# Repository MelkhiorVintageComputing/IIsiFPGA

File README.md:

# A FPGA on a IIsi PDS card...

## Goal

The goal of this repository is to be able to interface a modern (2023 era) [FPGA](https://en.wikipedia.org/wiki/Field-programmable_gate_array) with a [Macintosh IIsi](https://en.wikipedia.org/wiki/Macintosh_IIsi) using its PDS (Processor Direct Slot) connector. The PDS is basically just a physical connector to the MC68030 memory bus.

So unless you're a retrocomputing enthusiast with such a machine, this is useless. If you are such an enthusiast, then maybe the ability to connect a modern LCD monitor using a digital interface to an old Macintosh might be of interest to you.

This project was 'spun off' the [NuBusFPGA](https://github.com/rdolbeau/NuBusFPGA), a similar project for the NuBus used in several models of Macintosh of the era. NuBusFPGA itself is a spin-off of the [SBusFPGA](https://github.com/rdolbeau/SBusFPGA), a similar project for the SBus used in Sun's SPARCstation.

## Current status

The HDMI (Highly Desirable Macintosh Interface) is working, with both video (single-hardware-res, multi-depth, windowboxed lower res) & audio working. More details are available in the readme of the NuBusFPGA repository.

There's also experimental support to expose 240 MiB of DDR3 as additional memory to the host system, but that requires a patched ROM, typically using a modern Flash-based 'ROM SIMM'. Burst reads are supported for that use case, reading 16 bytes at a time from the DDR3 using a dedicated port, giving X-1-1-1 burst timings.

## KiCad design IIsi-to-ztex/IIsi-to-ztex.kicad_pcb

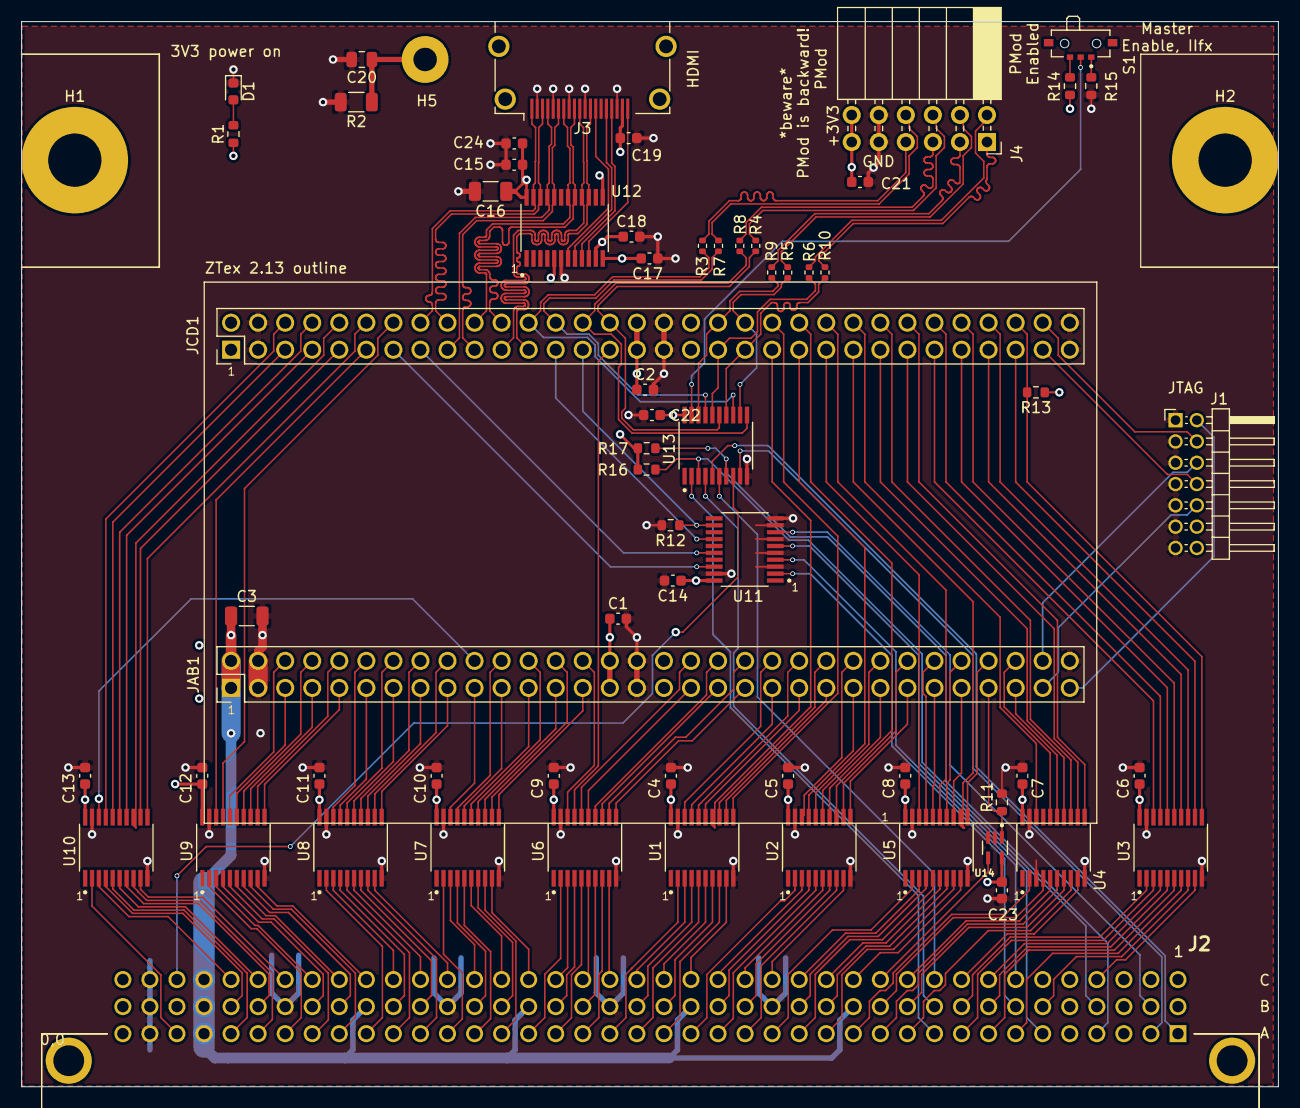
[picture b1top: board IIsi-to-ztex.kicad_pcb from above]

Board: 4 copper layers, 118.0 x 100.0 mm, 66 parts (0 on the bottom side), 218 nets.

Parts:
C1, C2, C4, C5, C6, C7, C8, C9, C10, C11, C12, C13, C14, C17, C18, C19, C21, C22, C23, C24: 100nF; C_0603_1608Metric
C3: 47uF 10V+; C_1206_3216Metric
C15: 10nF; C_0603_1608Metric
C16: 47uF 10V 1206; C_1206_3216Metric
C20: 10nF 1kV 0805; C_0805_2012Metric
D1: RED LED 0603; LED_0603_1608Metric
H1, H2: MountingHole_Pad; MountingHole_5mm_Pad
H5: MountingHole_Pad; MountingHole_2.2mm_M2_Pad
J1: Conn_02x07_Odd_Even; PinHeader_2x07_P2.00mm_Horizontal_For_SeeedStudio
J2: 650906-5; 6509065
J3: 10029449-111RLF (HDMI A); HDMI_A_Amphenol_10029449-111
J4: A2541HWR-2x6P (Pmod 2x6 F R); PinSocket_2x06_P2.54mm_Horizontal
JAB1: ZTEX_AB-ztex_AB; PinHeader_2x32_P2.54mm_Vertical_For_SeeedStudio
JCD1: ZTEX_CD-ztex_CD; PinHeader_2x32_P2.54mm_Vertical_For_SeeedStudio
R1: 560; R_0603_1608Metric
R2: 1M 500V 1206; R_1206_3216Metric
R3, R4, R5, R6, R7, R8, R9, R10: 22; R_0402_1005Metric
R11, R12, R13, R14, R15, R16, R17: 10k; R_0603_1608Metric
S1: SSAJ110100; SW_SSAJ110100
U1, U2, U3, U4, U5, U6, U7, U8, U9, U10, U11, U13: SN74CB3T3245PWR; SOP65P640X120-20N
U12: TPD12S016PWR; SOP65P640X120-24N
U14: SN74LV1T125DCKR; SOT65P210X110-5N

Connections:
+3V3: C1.1, C2.1, C4.1, C5.1, C6.1, C7.1, C8.1, C9.1, C10.1, C11.1, C12.1, C13.1, C14.1, C15.1, C16.1, C17.1, C21.1, C22.1, C23.2, C24.1, J4.11, J4.12, JAB1.29, JAB1.30, JAB1.33, JAB1.34, JCD1.31, JCD1.32, JCD1.35, JCD1.36, R1.1, R13.1, R14.1, U1.20, U2.20, U3.20, U4.20, U5.20, U6.20, U7.20, U8.20, U9.20, U10.20, U11.20, U12.5, U12.12, U12.24, U13.20, U14.5
+5V: C3.1, C18.1, J2.A37, J2.B13, J2.B19, J2.B25, J2.B31, J2.B37, J2.C37, JAB1.1, JAB1.2, R16.1, R17.1, U12.11
/B2B/JTAG_VIO: J1.2, JAB1.63
/HDMI/HDMI_5V: C19.1, J3.18, U12.13
/HDMI/cec_b: J3.13, U12.7
/HDMI/hpd_b: J3.19, U12.10
/HDMI/scl_b: J3.15, U12.8
/HDMI/sda_b: J3.16, U12.9
/pmod/P56+: J4.7, R7.1
/pmod/P56-: J4.8, R3.2
/pmod/P78+: J4.5, R8.1
/pmod/P78-: J4.6, R4.2
/pmod/P910+: J4.3, R9.1
/pmod/P910-: J4.4, R5.2
/pmod/P1112+: J4.1, R10.1
/pmod/P1112-: J4.2, R6.2
A0: J2.C36, U10.3
A0_3V3: JCD1.6, U10.17
A1: J2.B36, U10.4
A1_3V3: JCD1.5, U10.16
A2: J2.A36, U10.5
A2_3V3: JCD1.8, U10.15
A3: J2.C35, U10.6
A3_3V3: JCD1.7, U10.14
A4: J2.B35, U10.7
A4_3V3: JCD1.10, U10.13
A5: J2.A35, U10.8
A5_3V3: JCD1.9, U10.12
A6: J2.C34, U10.9
A6_3V3: JCD1.12, U10.11
A7: J2.A34, U9.2
A7_3V3: JCD1.11, U9.18
A8: J2.C33, U9.3
A8_3V3: JCD1.14, U9.17
A9: J2.B33, U9.4
A9_3V3: JAB1.6, U9.16
A10: J2.A33, U9.5
A10_3V3: JAB1.5, U9.15
A11: J2.C32, U9.6
A11_3V3: JAB1.8, U9.14
A12: J2.B32, U9.7
A12_3V3: JAB1.7, U9.13
A13: J2.A32, U9.8
A13_3V3: JAB1.10, U9.12
A14: J2.C31, U9.9
A14_3V3: JAB1.9, U9.11
A15: J2.A31, U8.2
A15_3V3: JAB1.12, U8.18
A16: J2.C30, U8.3
A16_3V3: JAB1.11, U8.17
A17: J2.B30, U8.4
A17_3V3: JAB1.14, U8.16
A18: J2.A30, U8.5
A18_3V3: JAB1.13, U8.15
A19: J2.C29, U8.6
A19_3V3: JAB1.16, U8.14
A20: J2.B29, U8.7
A20_3V3: JAB1.15, U8.13
A21: J2.A29, U8.8
A21_3V3: JAB1.18, U8.12
A22: J2.C28, U8.9
A22_3V3: JAB1.17, U8.11
A23: J2.A28, U7.2
A23_3V3: JAB1.19, U7.18
A24: J2.C27, U7.3
A24_3V3: JAB1.22, U7.17
A25: J2.B27, U7.4
A25_3V3: JAB1.21, U7.16
A26: J2.A27, U7.5
A26_3V3: JAB1.23, U7.15
A27: J2.C26, U7.6
A27_3V3: JAB1.24, U7.14
A28: J2.B26, U7.7
A28_3V3: JAB1.25, U7.13
A29: J2.A26, U7.8
A29_3V3: JAB1.26, U7.12
A30: J2.C25, U7.9
A30_3V3: JAB1.27, U7.11
A31: J2.A25, U6.2
A31_3V3: JAB1.28, U6.18
C16M: J2.C38, U13.8
C16M_3V3: JCD1.40, R5.1, U13.12
CACHE: J2.B2, U11.8
CACHE_3V3: JCD1.27, R12.1, U11.12
CPUCLK: J2.A38, U10.2
CPUCLK_3V3: JAB1.20, U10.18
D0: J2.A13, U4.2
D0_3V3: JCD1.48, U4.18
D1: J2.C13, U5.9
D1_3V3: JAB1.58, U5.11
D2: J2.A14, U5.8
D2_3V3: JCD1.47, U5.12
D3: J2.B14, U5.7
D3_3V3: JAB1.55, U5.13
D4: J2.C14, U5.6
D4_3V3: JAB1.56, U5.14
D5: J2.A15, U5.5
D5_3V3: JCD1.46, U5.15
D6: J2.B15, U5.4
D6_3V3: JAB1.53, U5.16
D7: J2.C15, U5.3
D7_3V3: JAB1.54, U5.17
D8: J2.A16, U5.2
D8_3V3: JCD1.45, U5.18
D9: J2.C16, U2.9
D9_3V3: JAB1.51, U2.11
D10: J2.A17, U2.8
D10_3V3: JAB1.52, U2.12
D11: J2.B17, U2.7
D11_3V3: JCD1.44, U2.13
D12: J2.C17, U2.6
D12_3V3: JAB1.49, U2.14
D13: J2.A18, U2.5
D13_3V3: JAB1.50, U2.15
D14: J2.B18, U2.4
D14_3V3: JCD1.43, U2.16
D15: J2.C18, U2.3
D15_3V3: JAB1.47, U2.17
D16: J2.A19, U2.2
D16_3V3: JAB1.48, U2.18
D17: J2.C19, U1.9
D17_3V3: JCD1.42, U1.11
D18: J2.A20, U1.8
D18_3V3: JAB1.45, U1.12
D19: J2.B20, U1.7
D19_3V3: JAB1.46, U1.13
D20: J2.C20, U1.6
D20_3V3: JCD1.41, U1.14
D21: J2.A21, U1.5
D21_3V3: JAB1.43, U1.15
D22: J2.B21, U1.4
D22_3V3: JAB1.44, U1.16
D23: J2.C21, U1.3
D23_3V3: JAB1.41, U1.17
D24: J2.A22, U1.2
D24_3V3: JAB1.42, U1.18
D25: J2.C22, U6.9
D25_3V3: JAB1.39, U6.11
D26: J2.A23, U6.8
D26_3V3: JAB1.40, U6.12
D27: J2.B23, U6.7
D27_3V3: JAB1.37, U6.13
D28: J2.C23, U6.6
D28_3V3: JAB1.38, U6.14
D29: J2.A24, U6.5
D29_3V3: JAB1.35, U6.15
D30: J2.B24, U6.4
D30_3V3: JAB1.36, U6.16
D31: J2.C24, U6.3
D31_3V3: JCD1.29, U6.17
FC0: J2.C11, U4.5
FC0_3V3: JAB1.59, U4.15
FC1: J2.B11, U4.7
FC1_3V3: JCD1.50, U4.13
FC2: J2.A11, U4.8
FC2_3V3: JCD1.51, U4.12
FPGA_JTAG_TCK: J1.6, JAB1.62
FPGA_JTAG_TDI: J1.10, JAB1.61
FPGA_JTAG_TDO: J1.8, JCD1.61
FPGA_JTAG_TMS: J1.4, JCD1.62
GND: C1.2, C2.2, C3.2, C4.2, C5.2, C6.2, C7.2, C8.2, C9.2, C10.2, C11.2, C12.2, C13.2, C14.2, C15.2, C16.2, C17.2, C18.2, C19.2, C20.2, C21.2, C22.2, C23.1, C24.2, D1.1, J1.1, J1.3, J1.5, J1.7, J1.9, J1.11, J1.13, J2.A39, J2.B16, J2.B22, J2.B28, J2.B34, J2.B39, J2.C39, J3.2, J3.5, J3.8, J3.11, J3.17, J4.9, J4.10, JAB1.3, JAB1.4, JAB1.31, JAB1.32, JAB1.64, JCD1.3, JCD1.4, JCD1.33, JCD1.34, JCD1.63, JCD1.64, R2.2, R11.2, R12.2, R15.1, U1.10, U1.19, U2.10, U2.19, U3.10, U3.19, U4.3, U4.10, U4.19, U5.10, U5.19, U6.10, U6.19, U7.10, U7.19, U8.10, U8.19, U9.10, U9.19, U10.10, U10.19, U11.3, U11.5, U11.7, U11.9, U11.10, U11.19, U12.6, U13.10, U14.2, U14.3
HDMI_CLK+: J3.10, JCD1.21, U12.16
HDMI_CLK-: J3.12, JCD1.23, U12.15
HDMI_D0+: J3.7, JCD1.20, U12.18
HDMI_D0-: J3.9, JCD1.22, U12.17
HDMI_D1+: J3.4, JCD1.17, U12.21
HDMI_D1-: J3.6, JCD1.19, U12.20
HDMI_D2+: J3.1, JCD1.16, U12.23
HDMI_D2-: J3.3, JCD1.18, U12.22
unnamed: D1.2, R1.2
unnamed: R14.2, S1.2
unnamed: R15.2, S1.1
PMOD-56+: JCD1.24, R7.2, U13.13
PMOD-56-: JCD1.26, R3.1, U13.17
PMOD-78+: JCD1.28, R8.2, U13.11
PMOD-78-: JCD1.30, R4.1, U13.15
PMOD-910+: JCD1.38, R9.2, U13.18
PMOD-1112+: JCD1.39, R10.2, U13.14
PMOD-1112-: JCD1.37, R6.1, U13.16
SHIELD: C20.1, H5.1, J3.SH, R2.1
SIZ0: J2.B9, U3.2
SIZ0_3V3: JCD1.53, U3.18
SIZ1: J2.A9, U3.3
SIZ1_3V3: JCD1.54, U3.17
~AS: J2.C9, U4.9
~AS_3V3: JCD1.52, U4.11
~BERR: J2.B12, U4.4
~BERR_3V3: JAB1.60, U4.16
~BG: J2.B10, U13.4
~BGACK: J2.A10, U13.2
~BR: J2.C10, U13.6
~CBACK: J2.B7, U11.2
~CBACK_3V3: JCD1.13, U11.18
~CBREQ: J2.C7, U11.4
~CBREQ_3V3: JCD1.15, U11.16
~CIOUT: J2.A6, U11.6
~CIOUT_3V3: JCD1.25, U11.14
~DS: J2.B6, U3.8
~DSACK0: J2.B8, U3.5
~DSACK0_3V3: JCD1.56, U3.15
~DSACK1: J2.A8, U3.6
~DSACK1_3V3: JCD1.57, U3.14
~DS_3V3: JCD1.59, U3.12
~FPU: J2.A2, U13.9
~HALT: J2.C12, U14.4
~HALT_3V3: JAB1.57, R11.1, U14.1
~IRQ1: J2.C4, U3.9
~IRQ1_3V3: JCD1.60, R13.2, U3.11
~IRQ2: J2.B4, R16.2, U13.3
~IRQ3: J2.A4, R17.2, U13.7
~MASTER_OE: S1.C, U13.19
~RBV: J2.A1, U13.5
~RESET: J2.A12, U4.6
~RESET_3V3: JCD1.49, U4.14
~RW: J2.C8, U3.4
~RW_3V3: JCD1.55, U3.16
~STERM: J2.A7, U3.7
~STERM_3V3: JCD1.58, U3.13

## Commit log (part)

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2023-04-01 import draft to GH
2023-04-01 start work on simul
2023-04-01 readme
2023-04-01 rework /HALT
2023-04-01 change of pins
2023-04-01 handle /halt, wait for locked PLL
2023-05-16 cleanup DRC
2023-05-27 extra stuff
2023-05-27 3V3 SRAM draft
2023-05-28 missing file
2023-06-03 pcb upd
2023-06-03 connect rbv to last pmod pin
2023-06-03 some rerouting
2023-06-04 minro cleanups
2023-06-06 some pull-(up,down)s
2023-06-13 catching up with PCB
2023-06-25 early bringup
2023-06-25 cleanup, map memory in superslot (for now)
2023-06-25 more mapping, fix partial write
2023-06-26 write FIFO
2023-07-01 first attempt at burst ; but so far mapping through TT0 doesn't seem to enable burst (though regular accesses work)
2023-07-01 some fixes, but burst doesn't work properly
2023-07-02 fix burst mode
2023-07-23 push update that supports memory mode, with tons of leftovers debug code
2023-07-23 move memory expansion mapping back to (instead of -bash8)
2023-08-15 first go at crypto co-pro, copro iface seems OK but crypto still wrong (endianess?)
2023-08-15 oups, backward inputs
2023-08-15 fx some endianess
2023-08-15 fix endianess, LGTM
2023-08-15 just in case
2023-08-17 optional in-copro state
2023-08-19 mmmm, FloCoPo?
2023-08-20 less code duplication
2023-08-20 fixes
2023-08-20 fp-to-fp
2023-08-20 reorg
2023-08-20 div, sub (as a+(-b)), neg, abs, missing files
2023-08-20 mfmovecr
2023-09-16 license
2023-11-18 move some of board platform stuff to common
2023-11-19 move stuff in common as for the others; need to work on rd68891's decrypt stuff
2023-12-02 debug stuff
2023-12-02 upd common
2023-12-02 add ref
2023-12-02 subdir
2024-02-02 pmod orientation
2024-02-17 catch-up for progammable clock
2024-02-23 drop moved file
2024-02-24 updat e REF
2024-02-24 uppdate/expand flopoco files, flag instruciton not implemented on '040
2024-05-18 IIfx support (needs its own bitstream), board-based name
2024-05-18 IIfx support, fast slew on D/STERM, stronger drive on STERM, need to think more about this...
2024-09-01 down-conversion from Motorola's FP80 to IEEE FP32/FP64 (from patched flopoco)
2024-09-07 fmovem (data register)
2024-09-07 move const table to native flopoco format
2024-09-08 some FPSR bits, plus first draft of conditionals (untested)
2024-09-14 some level of support for FPSR (w/ minimal branch testing done)
2024-09-14 committing fixed OutputIEEE
2024-09-14 fix multi-ctrl order, implement ea->ctrl dialog
2024-09-15 pseudo-save/restore
2024-09-22 react properly to operand partial write
2024-09-22 fmove to fp w/ integer input (using flopoco 4.1.1 Fix2FP operator)
2024-09-24 longword output (byte/word not rounded properly)
2025-09-06 timing file for testing
2025-09-06 mmm, BCD?
2026-01-06 comments
2026-02-22 From Template
2026-03-21 fix BoM
2026-03-25 minor fix
2026-03-25 various updates
2026-03-25 V3.0 board files
2026-03-25 do files, submodule
2026-03-25 produciton files
2026-03-25 status
2026-03-28 update v1 do
2026-03-28 unify leds naming with IIsiA7 Mini
2026-03-28 cleanup
2026-03-28 grr, fix pin order
2026-03-29 minor cleanups
